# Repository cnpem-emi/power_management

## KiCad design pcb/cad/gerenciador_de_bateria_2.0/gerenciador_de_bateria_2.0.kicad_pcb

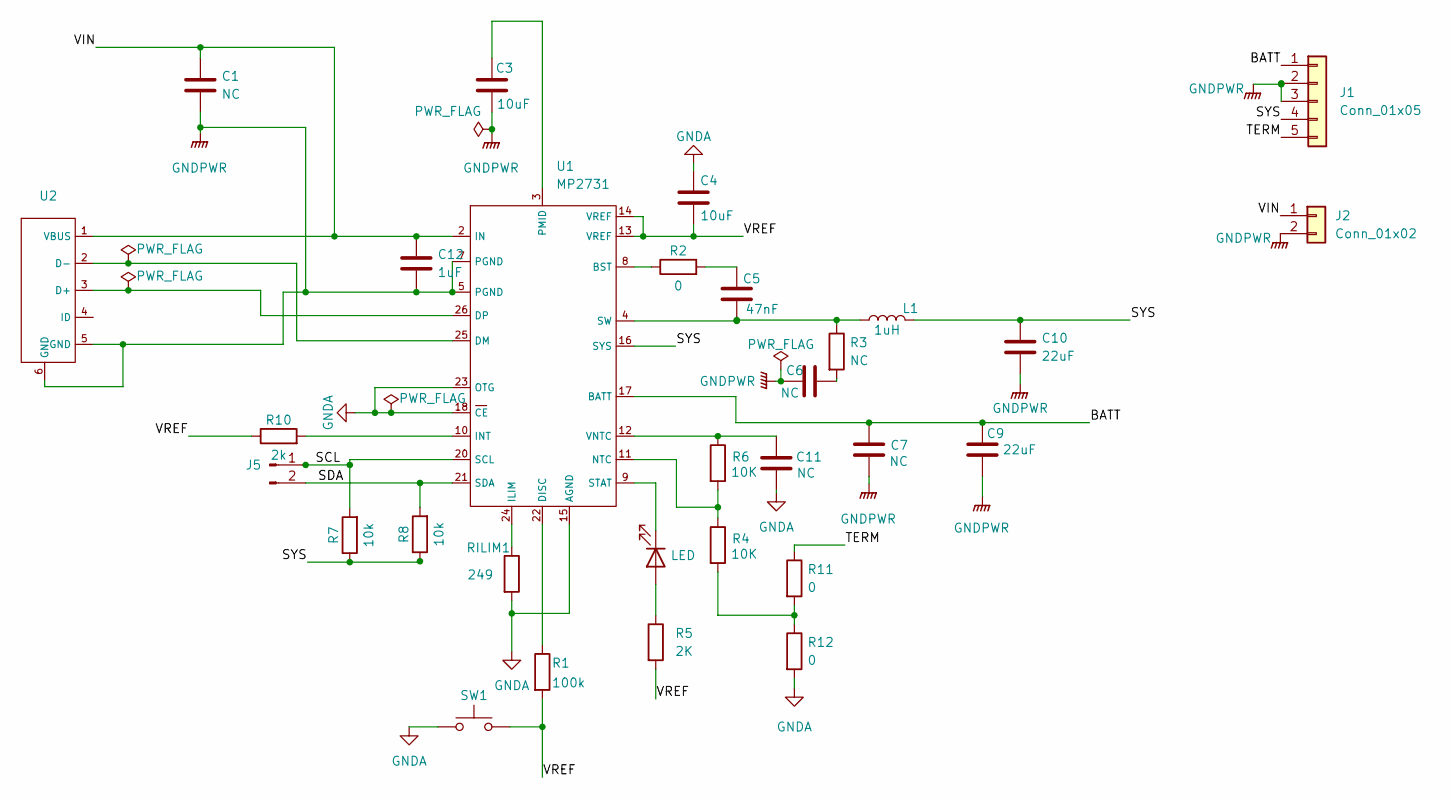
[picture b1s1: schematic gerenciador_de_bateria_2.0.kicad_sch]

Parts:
C1, C6, C7, C11: NC; C_0805_2012Metric
C3, C4: 10uF; C_0805_2012Metric
C5: 47nF; C_0805_2012Metric
C9, C10: 22uF; C_0805_2012Metric
C12: 1uF; C_0805_2012Metric
D1: LED; LED_0805_2012Metric
J1: Conn_01x05; PinHeader_1x05_P2.54mm_Vertical
J2: Conn_01x02; PinHeader_1x02_P2.54mm_Vertical
J5: Conn_01x02_Male; PinHeader_1x02_P2.54mm_Vertical
L1: 1uH; L_1210_3225Metric
R1: 100k; R_0805_2012Metric
R2, R11, R12: 0; R_0805_2012Metric
R3: NC; R_0805_2012Metric
R4, R6: 10K; R_0805_2012Metric
R5: 2K; R_0805_2012Metric
R7, R8: 10k; R_0805_2012Metric
R10: 2k; R_0805_2012Metric
RILIM1: 249; R_0805_2012Metric
SW1: SW_Push; SW_SPST_B3U-1000P
U1: MP2731; QFN-26_MP2731
U2: USB_BQ25629; USB_Micro-B_Amphenol_10118194_Horizontal

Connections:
/BATT: C7.1, C9.2, J1.1, U1.17 (BATT)
/SCL: J5.1, R7.2, U1.20 (SCL); also elsewhere on the board
/SDA: J5.2, R8.2, U1.21 (SDA); also elsewhere on the board
/SYS: C10.1, J1.4, L1.2, R7.1, R8.1, U1.16 (SYS)
/TERM: J1.5, R11.1
/VIN: C1.1, C12.1, J2.1, U1.2 (IN), U2.1 (VBUS); also elsewhere on the board
/VREF: C4.1, R1.2, R5.2, R10.1, SW1.2, U1.13 (VREF), U1.14 (VREF)
GNDA: C4.2, C11.1, R12.2, RILIM1.2, SW1.1, U1.15 (AGND), U1.18 (CE), U1.23 (OTG)
GNDPWR: C1.2, C3.2, C6.2, C7.2, C9.1, C10.2, C12.2, J1.2, J1.3, J2.2, U1.5 (PGND), U1.7 (PGND), U2.5 (GND), U2.6 (GND); also elsewhere on the board
unnamed: C3.1, U1.3 (PMID)
unnamed: C5.1, R2.2
unnamed: C5.2, L1.1, R3.1, U1.4 (SW)
unnamed: C6.1, R3.2
unnamed: C11.2, R6.1, U1.12 (VNTC)
unnamed: D1.1 (K), U1.9 (STAT)
unnamed: D1.2 (A), R5.1
unnamed: R1.1, U1.22 (DISC)
unnamed: R2.1, U1.8 (BST)
unnamed: R4.1, R6.2, U1.11 (NTC)
unnamed: R10.2, U1.10 (INT)
unnamed: R4.2, R11.2, R12.1
unnamed: RILIM1.1, U1.24 (ILIM)
unnamed 22: U1.25 (DM), U2.2 (D-); also elsewhere on the board
unnamed 23: U1.26 (DP), U2.3 (D+); also elsewhere on the board

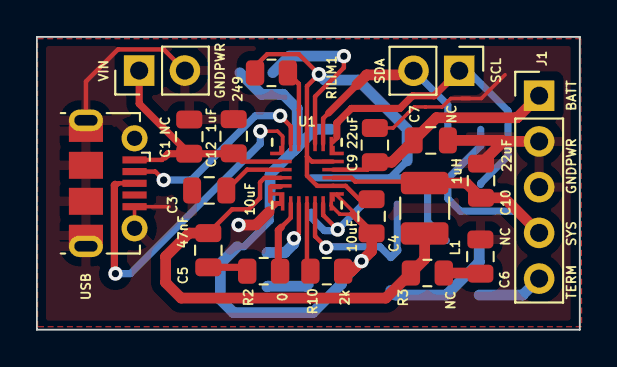
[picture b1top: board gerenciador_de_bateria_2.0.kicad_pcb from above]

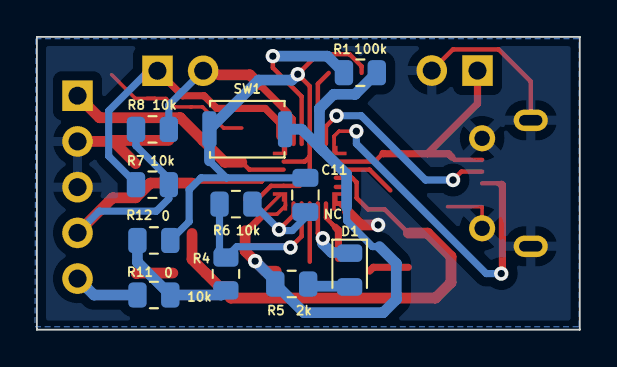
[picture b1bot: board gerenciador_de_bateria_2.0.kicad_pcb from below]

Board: 2 copper layers, 30.2 x 16.3 mm, 30 parts (11 on the bottom side), 24 nets.

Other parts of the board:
GNDPWR: Conn_01x02; PinHeader_1x02_P2.54mm_Vertical
SDA: Conn_01x02_Male; PinHeader_1x02_P2.54mm_Vertical
USB: USB_BQ25629; USB_Micro-B_Molex-105017-0001

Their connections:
/SCL: SDA.1; also elsewhere on the board
/SDA: SDA.2; also elsewhere on the board
/VIN: GNDPWR.1, USB.1 (VBUS); also elsewhere on the board
GNDPWR: GNDPWR.2, USB.5 (GND), USB.6 (GND); also elsewhere on the board
unnamed 22: USB.2 (D-); also elsewhere on the board
unnamed 23: USB.3 (D+); also elsewhere on the board

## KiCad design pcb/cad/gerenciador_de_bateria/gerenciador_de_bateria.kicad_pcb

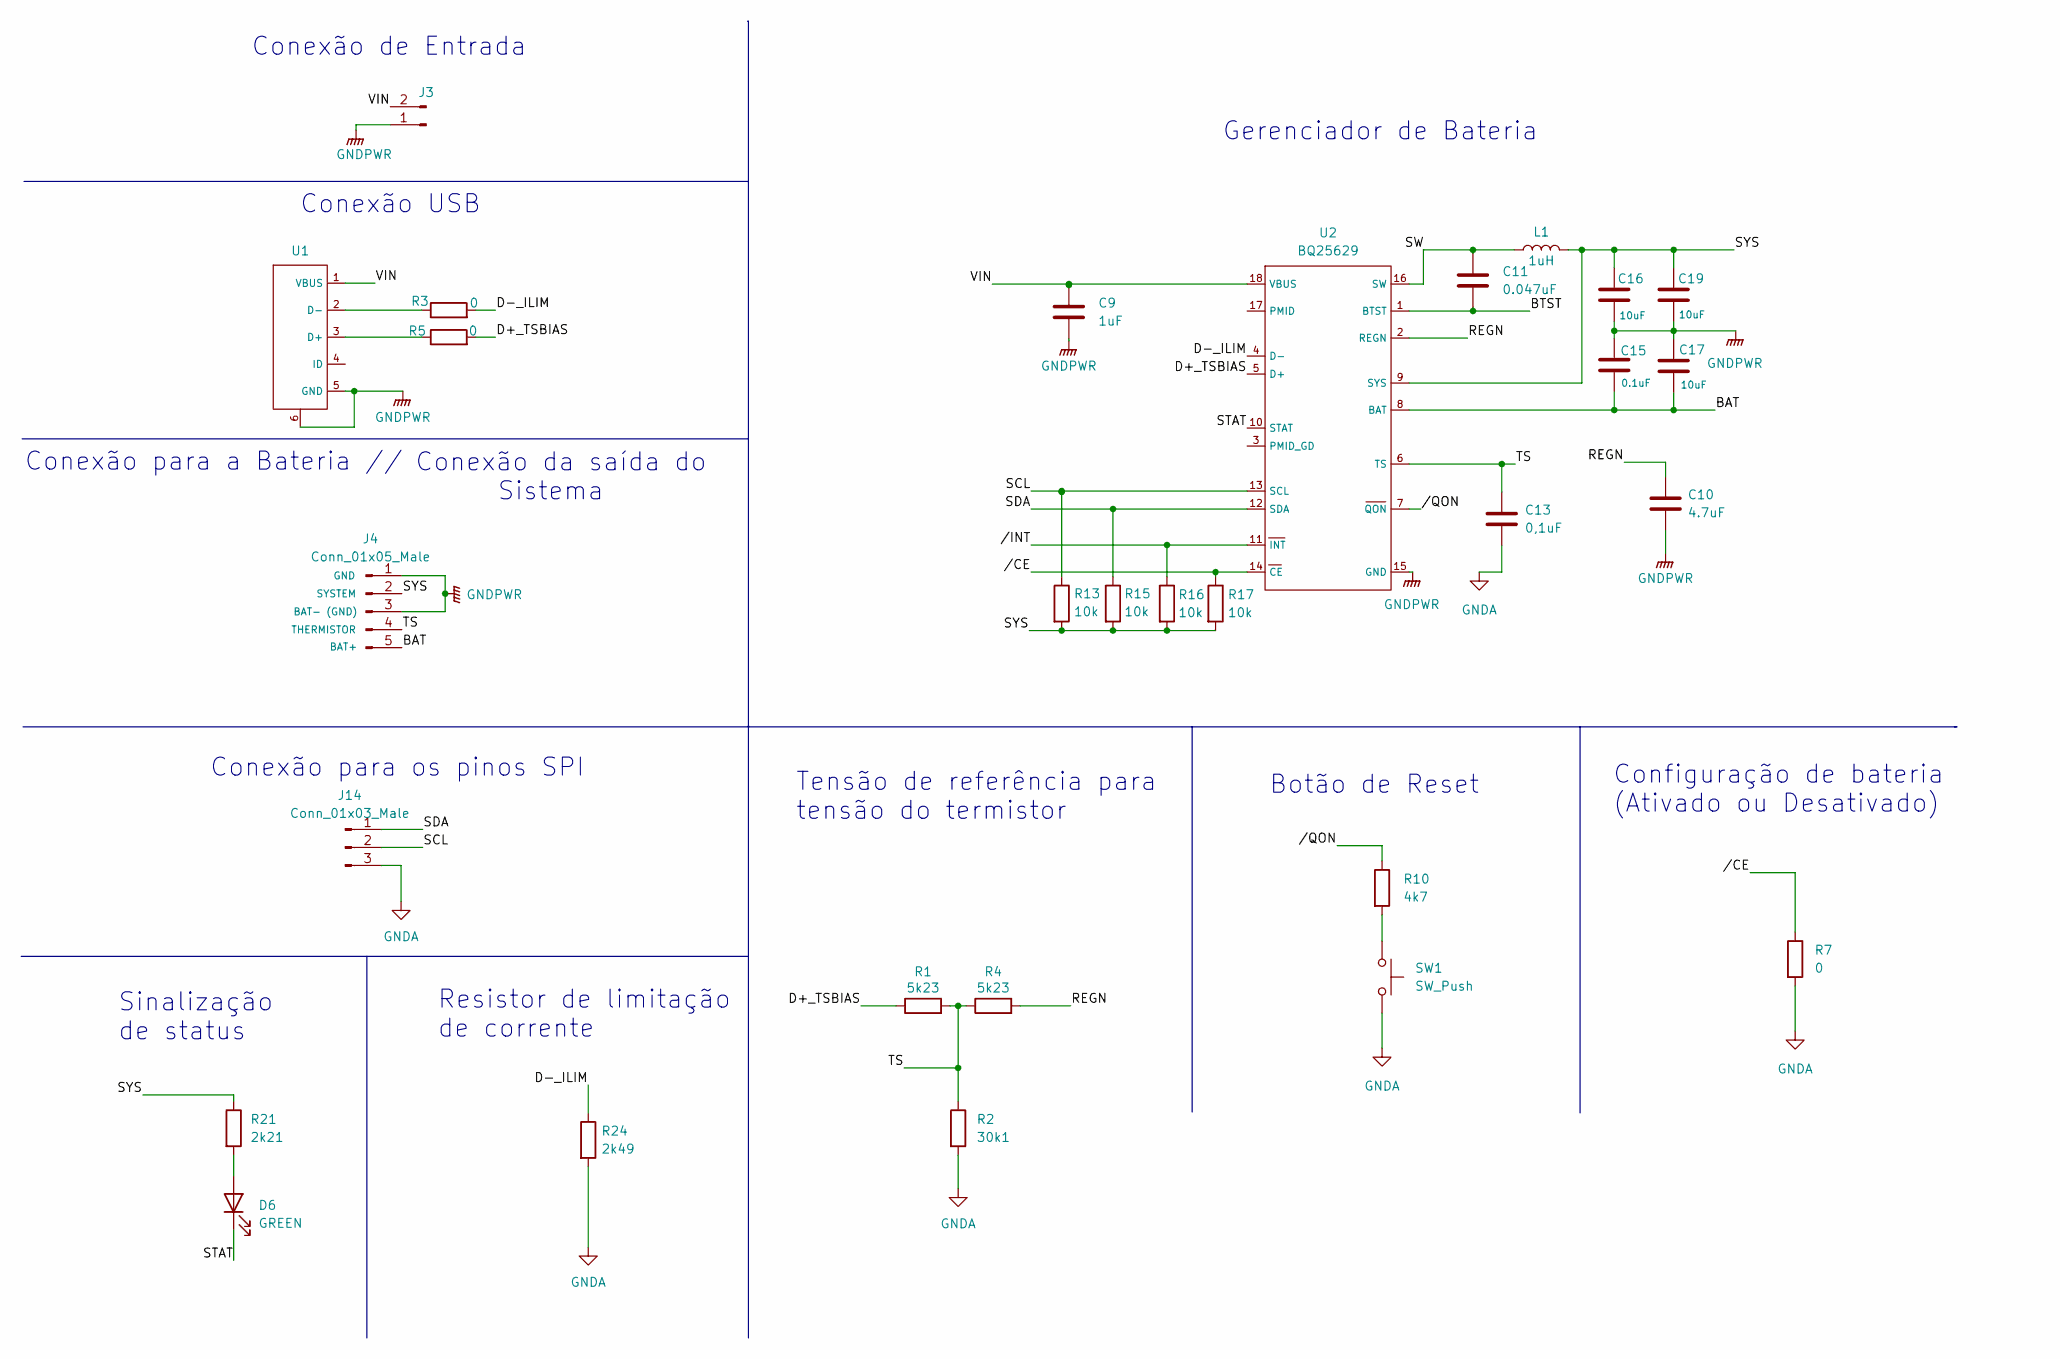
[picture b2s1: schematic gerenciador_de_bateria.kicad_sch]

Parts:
C9: 1uF; C_0805_2012Metric
C10: 4.7uF; C_0805_2012Metric
C11: 0.047uF; C_0805_2012Metric
C13: 0,1uF; C_0805_2012Metric
C15: 0.1uF; C_0805_2012Metric
C16, C17, C19: 10uF; C_0805_2012Metric
D6: GREEN; LED_0805_2012Metric
J3: Conn_01x02_Male; PinHeader_1x02_P2.54mm_Vertical
J4: Conn_01x05_Male; PinHeader_1x05_P2.54mm_Vertical
J14: Conn_01x03_Male; PinHeader_1x03_P2.54mm_Vertical
L1: 1uH; L_1210_3225Metric
R1, R4: 5k23; R_0805_2012Metric
R2: 30k1; R_0805_2012Metric
R3, R5, R7: 0; R_0805_2012Metric
R10: 4k7; R_0805_2012Metric
R13, R15, R16, R17: 10k; R_0805_2012Metric
R21: 2k21; R_0805_2012Metric
R24: 2k49; R_0805_2012Metric
SW1: SW_Push; SW_SPST_B3U-1000P
U1: USB_BQ25629; USB_Micro-B_Amphenol_10118194_Horizontal
U2: BQ25629; WQFN-HR18_RYK_TEX

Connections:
/BAT: C15.2, C17.2, J4.5, U2.8 (BAT)
/BTST: C11.2, U2.1 (BTST)
/D+_TSBIAS: R1.1, R5.2, U2.5 (D+)
/D-_ILIM: R3.2, R24.1, U2.4 (D-)
/REGN: C10.1, R4.2, U2.2 (REGN)
/SCL: J14.2, R13.1, U2.13 (SCL)
/SDA: J14.1, R15.1, U2.12 (SDA)
/STAT: D6.1 (K), U2.10 (STAT)
/SW: C11.1, L1.1, U2.16 (SW)
/SYS: C16.1, C19.1, J4.2, L1.2, R13.2, R15.2, R16.2, R17.2, R21.1, U2.9 (SYS)
/TS: C13.1, J4.4, R1.2, R2.1, R4.1, U2.6 (TS)
/VIN: C9.1, J3.2, U1.1 (VBUS), U2.18 (VBUS)
//CE: R7.1, R17.1, U2.14 (CE)
//INT: R16.1, U2.11 (INT)
//QON: R10.1, U2.7 (QON)
GNDA: C13.2, J14.3, R2.2, R7.2, R24.2, SW1.2
GNDPWR: C9.2, C10.2, C15.1, C16.2, C17.1, C19.2, J3.1, J4.1, J4.3, U1.5 (GND), U1.6, U2.15 (GND)
unnamed: D6.2 (A), R21.2
unnamed: R3.1, U1.2 (D-)
unnamed: R5.1, U1.3 (D+)
unnamed: R10.2, SW1.1

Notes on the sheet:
Conexão para a Bateria //
Sinalização de status
Configuração de bateria (Ativado ou Desativado)
Gerenciador de Bateria
Conexão de Entrada
Tensão de referência para tensão do termistor
Conexão USB
Resistor de limitação de corrente
Conexão para os pinos SPI
Botão de Reset
Conexão da saída do Sistema

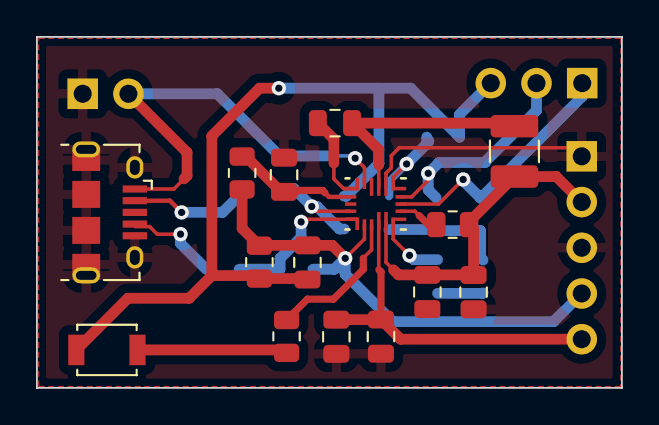
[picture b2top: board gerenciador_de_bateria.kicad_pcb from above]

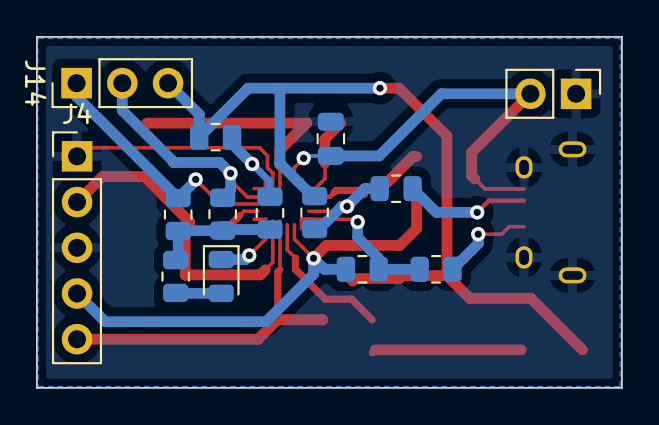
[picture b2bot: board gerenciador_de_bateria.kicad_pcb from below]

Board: 2 copper layers, 32.5 x 19.5 mm, 29 parts (14 on the bottom side), 21 nets.

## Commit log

2023-08-01 upload dos arquivos esquemáticos das PCBs para os gerenciadores de bateria
2023-08-02 Atualização dos esquemáticos de PCB para gerenciadores de bateria
2023-08-03 Atualização dos esquemáticos dos gerenciadores de bateria
2023-08-03 Atualização nas conexões do pino NTC
2023-08-08 Associação dos footprint e início do layout da PCB
2023-08-08 Associação de footprints e inicio do layout de pCB.
2023-08-09 Alteração no GND do esquemático para GNDA ou GNDPWR, finalização da PCB do gerenciador de bateria 2.0
2023-08-09 Inicio do layout de PCB
2023-08-10 Otimização do esquemático do gerenciador_de_bateria, PCB atualizada com o USB centralizado no gerenciador_de_bateria_2.0, no gerenciador_de_bateria a PCB foi inicializada e finalizada
2023-08-10 Alterações no lauout de PCB
2023-08-11 Alterações no lauout de PCB do MP2731
2023-08-14 Otimização e diminuição da PCB do gerenciador_de_bateria
2023-08-14 Atualização da placa para gerenciamento de bateria, finalização do layout e roteamento
2023-08-17 Alteração dos conectores no esquemático para o rearranjo e a diminuição da PCB que foi feita no gerenciador_de_bateria
2023-10-04 Revisão da PCB do gerenciador de bateria 2.0, corrigindo os GND que estavam flutuando e atualizando footprint de componentes que estavam errados
2023-10-05 Atualização na PCB do gerenciador de bateria 2.0, após mais uma revisão para fabricação da placa, alterando apenas as identificações de cada componente, mantendo um padrão
2023-11-09 Panelização do gerenciador_de_bateria_2.0 para fabricação
